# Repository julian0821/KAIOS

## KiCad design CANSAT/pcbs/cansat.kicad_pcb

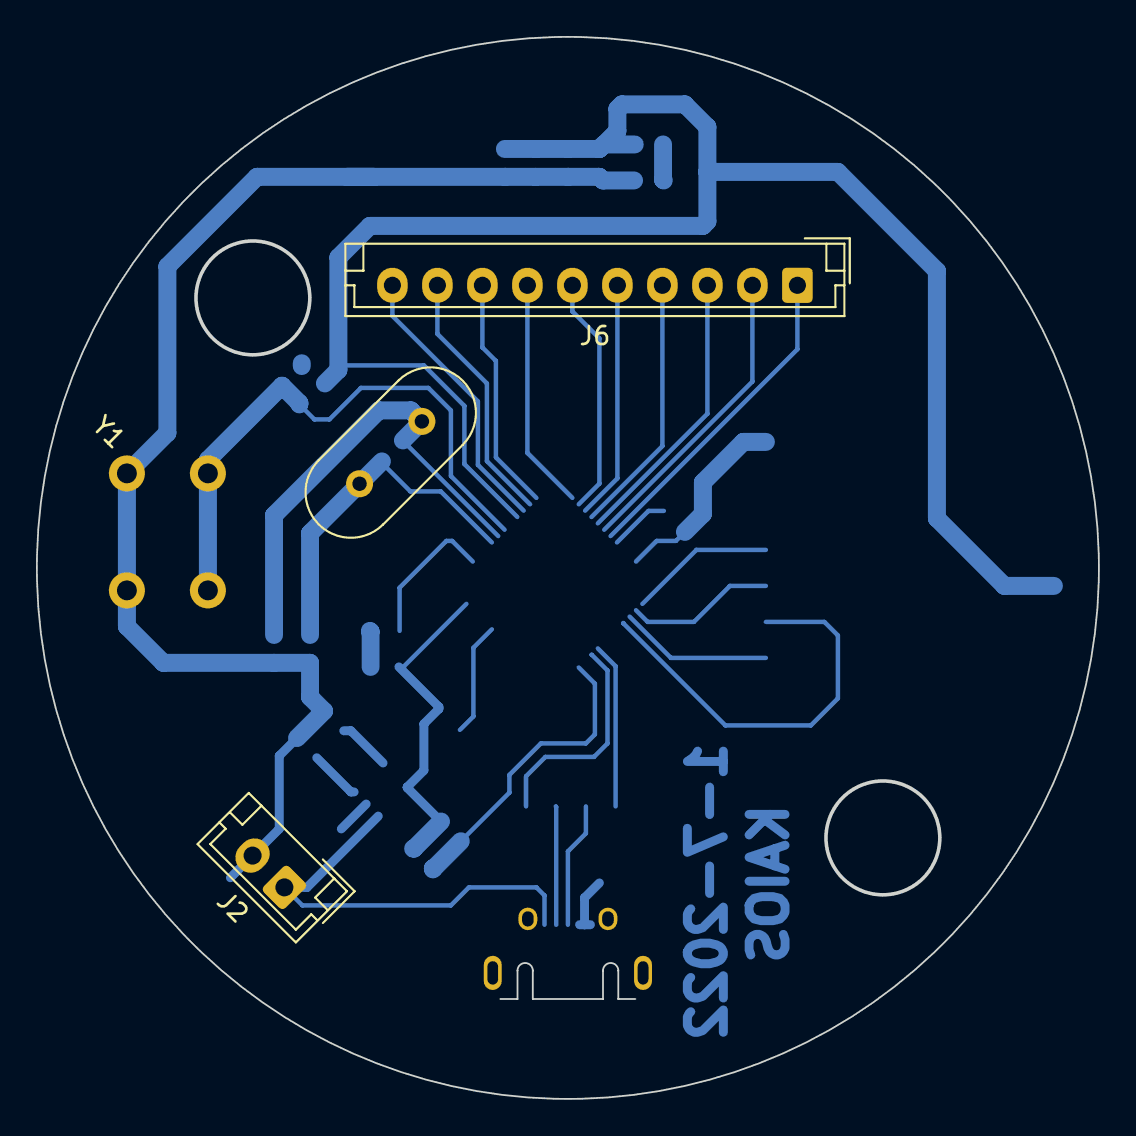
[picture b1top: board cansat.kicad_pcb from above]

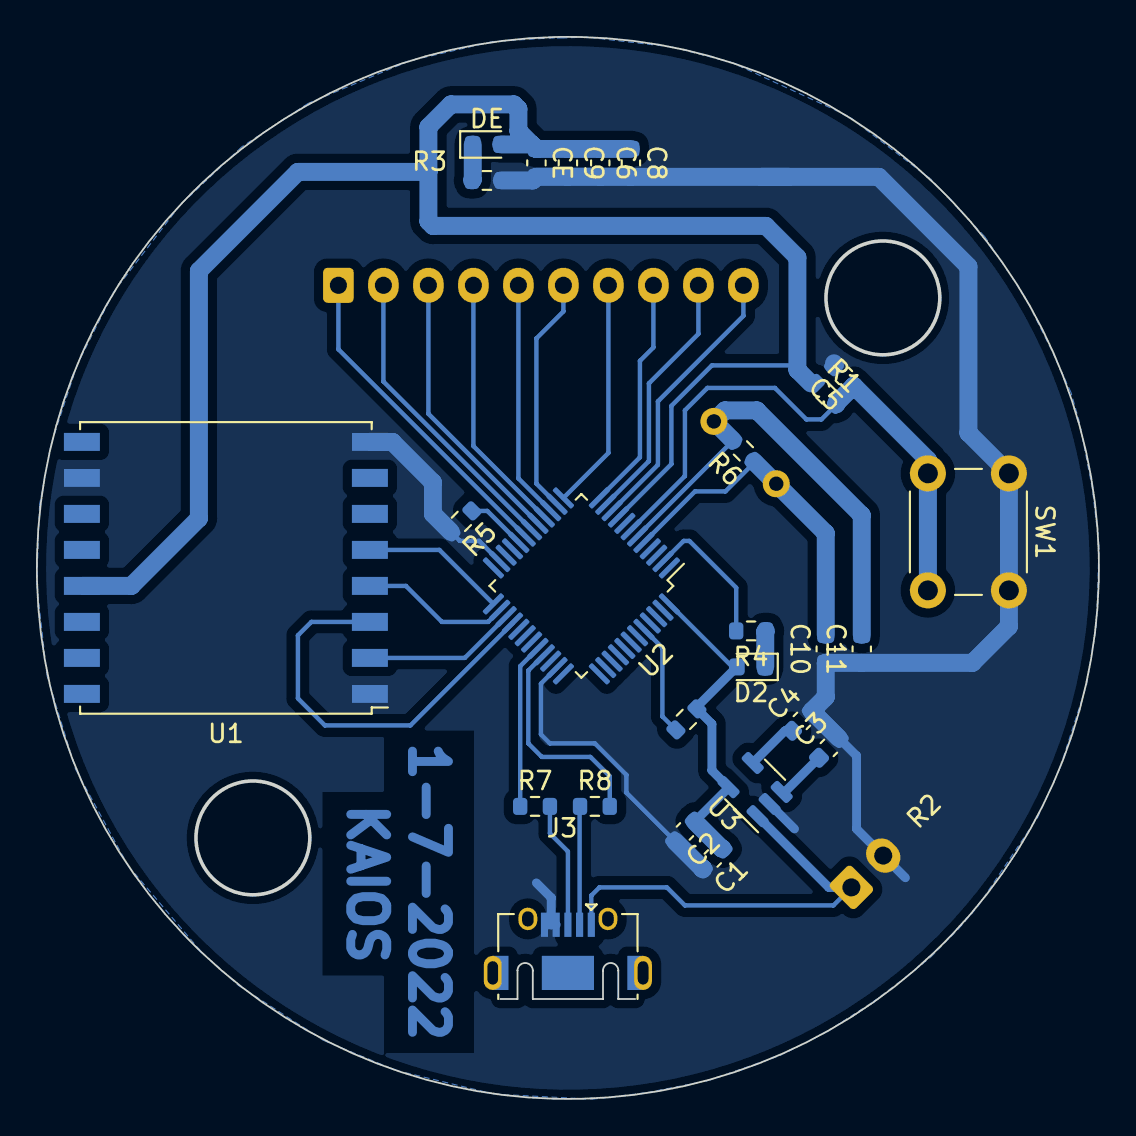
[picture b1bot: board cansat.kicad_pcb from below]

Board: 2 copper layers, 58.9 x 58.9 mm, 29 parts (26 on the bottom side), 30 nets.

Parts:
C1: 106u; C_0603_1608Metric
C2, C6, C8, C9: 104u; C_0603_1608Metric
C3, C5: 105u; C_0603_1608Metric
C4: 223u; C_0603_1608Metric
C10, C11: 20p; C_0603_1608Metric
CE: 104u; C_0603_1608Metric
D2: LED; LED_0603_1608Metric
DE: LED; LED_0603_1608Metric
J2: Battery; JST_EH_B2B-EH-A_1x02_P2.50mm_Vertical
J3: USB_B_Micro; USB_Micro-AB_Molex_47590-0001
J6: Conn_01x10; JST_EH_B10B-EH-A_1x10_P2.50mm_Vertical
R1: 10K; R_0603_1608Metric
R2, R5, R7, R8: 100K; R_0603_1608Metric
R3, R4: 510; R_0603_1608Metric
R6: 1M; R_0603_1608Metric
SW1: SW_Push; SW_PUSH_6mm
U1: RFM95W-868S2; HOPERF_RFM9XW_SMD
U2: STM32F103C8T6; LQFP-48_7x7mm_P0.5mm
U3: RT9193-33; TSOT-23-5
Y1: 8M; Crystal_HC18-U_Vertical

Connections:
/3V3: C1.1, C2.1, C6.1, C8.1, C9.1, CE.1, D2.2 (A), DE.2 (A), R1.1, R2.1, U1.13 (3.3V), U2.9 (VDDA), U2.24 (VDD), U2.36 (VDD), U2.48 (VDD), U3.5 (VOUT)
/5V: C3.1, J2.1, J3.1 (VBUS), U3.1 (VIN), U3.3 (EN)
/A0: J6.10, U2.10 (PA0)
/A1: J6.9, U2.11 (PA1)
/A2: J6.8, U2.12 (PA2)
/A3: J6.7, U2.13 (PA3)
/A4: J6.6, U2.14 (PA4)
/A5: J6.5, U2.15 (PA5)
/A6: J6.4, U2.16 (PA6)
/A7: J6.3, U2.17 (PA7)
/B0: J6.2, U2.18 (PB0)
/B1: J6.1, U2.19 (PB1)
/BOOT0: R2.2, U2.44 (BOOT0)
/BOOT1: R5.1, U2.20 (PB2)
/MISO: U1.2 (MISO), U2.27 (PB14)
/MOSI: U1.3 (MOSI), U2.28 (PB15)
/NSS: U1.5 (NSS), U2.25 (PB12)
/OSC_IN: C10.2, R6.1, U2.5 (PD0), Y1.1
/OSC_OUT: C11.2, R6.2, U2.6 (PD1), Y1.2
/PA11: R7.1, U2.32 (PA11)
/PA12: R8.2, U2.33 (PA12)
/PC13: R4.2, U2.2 (PC13)
/RESET: C5.1, R1.2, SW1.2, U2.7 (NRST)
/SCK: U1.4 (SCK), U2.26 (PB13)
GND: C1.2, C2.2, C3.2, C4.2, C5.2, C6.2, C8.2, C9.2, C10.1, C11.1, CE.2, J2.2, J3.4 (ID), J3.5 (GND), R3.2, R5.2, SW1.1, U1.1 (GND), U1.8 (GND), U1.10 (GND), U2.8 (VSSA), U2.23 (VSS), U2.35 (VSS), U2.47 (VSS), U3.2 (GND)
unnamed: C4.1, U3.4 (BP)
unnamed: DE.1 (K), R3.1
unnamed: D2.1 (K), R4.1
unnamed: J3.2 (D-), R8.1
unnamed: J3.3 (D+), R7.2
